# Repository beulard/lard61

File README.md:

# lard61

A custom 60% ansi keyboard PCB.

+ [RP2040](https://www.raspberrypi.com/documentation/microcontrollers/rp2040.html)
+ 4MB flash
+ 12MHz crystal
+ USB-C
+ full n-key rollover
+ a single LED

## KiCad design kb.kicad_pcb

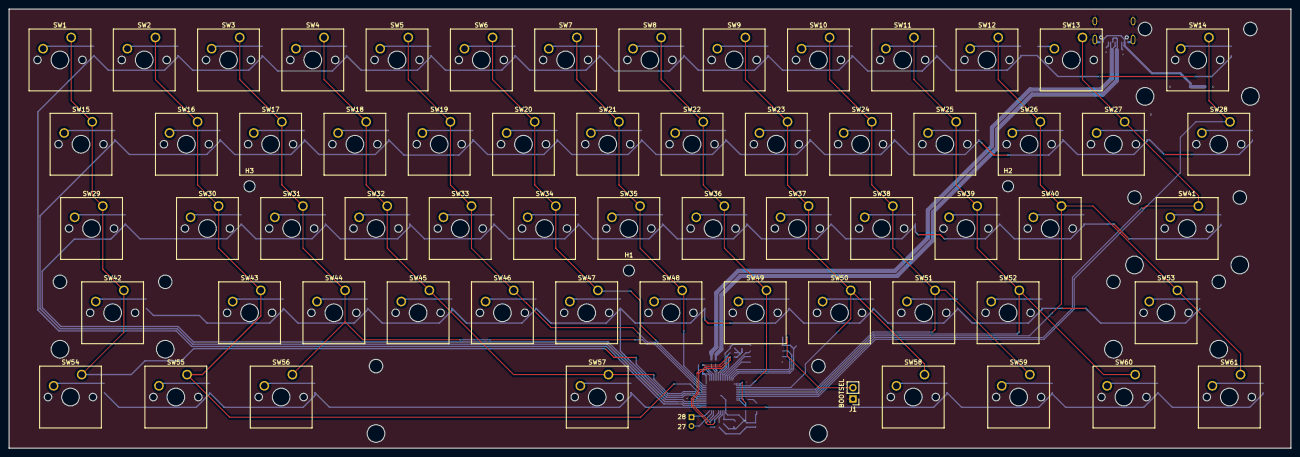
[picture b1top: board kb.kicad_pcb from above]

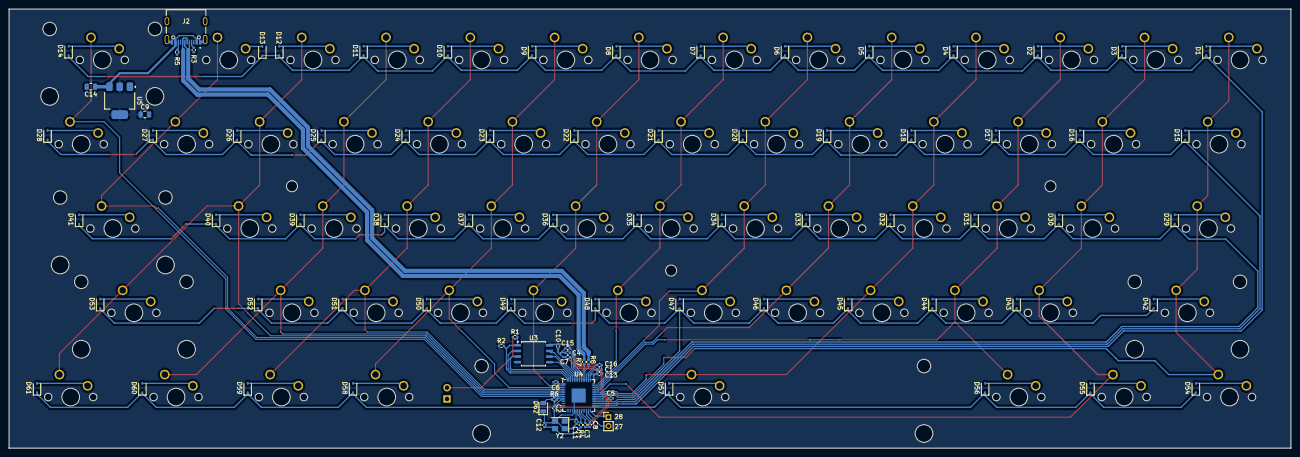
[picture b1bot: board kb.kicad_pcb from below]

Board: 2 copper layers, 289.8 x 99.2 mm, 157 parts (92 on the bottom side), 104 nets.

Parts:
C1, C16: 1u; C_0402_1005Metric
C2, C3, C4, C5, C6, C7, C8, C10, C13, C15: 100n; C_0402_1005Metric
C9, C14: 10u; C_0805_2012Metric
C11, C12: 15p; C_0402_1005Metric
D1, D2, D3, D4, D5, D6, D7, D8, D9, D10, D11, D12, D13, D14, D15, D16, D17, D18, D19, D20, D21, D22, D23, D24, D25, D26, D27, D28, D29, D30, D31, D32, D33, D34, D35, D36, D37, D38, D39, D40, D41, D42, D43, D44, D45, D46, D47, D48, D49, D50, D51, D52, D53, D54, D55, D56, D57, D58, D59, D60, D61: D; D_SOD-323
D62: LED; LED_0805_2012Metric
H1, H2, H3: MountingHole; MountingHole_2.5mm
J1: DNP; PinHeader_1x02_P2.54mm_Vertical
J2: KH-TYPE-C-16P; KINGHELM_KH-TYPE-C-16P
J5: DNP; PinHeader_1x02_P2.00mm_Vertical
R1, R4: 1k; R_0402_1005Metric
R2: DNP; R_0402_1005Metric
R3, R5: 5.1k; R_0402_1005Metric
R6: 470; R_0402_1005Metric
R7, R8: 27.4; R_0402_1005Metric
SW1, SW2, SW3, SW4, SW5, SW6, SW7, SW8, SW9, SW10, SW11, SW12, SW13, SW16, SW17, SW18, SW19, SW20, SW21, SW22, SW23, SW24, SW25, SW26, SW27, SW30, SW31, SW32, SW33, SW34, SW35, SW36, SW37, SW38, SW39, SW40, SW43, SW44, SW45, SW46, SW47, SW48, SW49, SW50, SW51, SW52: DNP; SW_Cherry_MX_1.00u_PCB
SW14: DNP; SW_Cherry_MX_2.00u_PCB
SW15, SW28: DNP; SW_Cherry_MX_1.50u_PCB
SW29: DNP; SW_Cherry_MX_1.75u_PCB
SW41, SW42: DNP; SW_Cherry_MX_2.25u_PCB
SW53: DNP; SW_Cherry_MX_2.75u_PCB
SW54, SW55, SW56, SW58, SW59, SW60, SW61: DNP; SW_Cherry_MX_1.25u_PCB
SW57: DNP; SW_Cherry_MX_6.25u_PCB
U3: W25Q32JVSS; SOIC-8_5.23x5.23mm_P1.27mm
U4: RP2040; QFN-56-1EP_7x7mm_P0.4mm_EP3.2x3.2mm
U5: NCP1117-3.3_SOT223; SOT-223-3_TabPin2
Y2: ABM8-272-T3; Crystal_SMD_Abracon_ABM8G-4Pin_3.2x2.5mm

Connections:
+1V1: C7.1, C8.1, C16.1, U4.23 (DVDD), U4.45 (VREG_VOUT), U4.50 (DVDD)
+3V3: C1.1, C2.1, C3.1, C4.1, C5.1, C6.1, C9.1, C10.1, C13.1, C15.1, R2.1, U3.8 (VCC), U4.1 (IOVDD), U4.10 (IOVDD), U4.22 (IOVDD), U4.26 (RUN), U4.33 (IOVDD), U4.42 (IOVDD), U4.43 (ADC_AVDD), U4.44 (VREG_IN), U4.48 (USB_VDD), U4.49 (IOVDD), U5.2 (VO)
/GPIO0: SW8.1, SW22.1, SW36.1, SW49.1, U4.2 (GPIO0)
/GPIO1: SW9.1, SW23.1, SW37.1, SW50.1, SW58.1, U4.3 (GPIO1)
/GPIO2: SW10.1, SW24.1, SW38.1, SW51.1, SW59.1, U4.4 (GPIO2)
/GPIO3: SW11.1, SW25.1, SW39.1, SW52.1, SW60.1, U4.5 (GPIO3)
/GPIO4: SW12.1, SW26.1, SW40.1, SW53.1, SW61.1, U4.6 (GPIO4)
/GPIO5: SW13.1, SW27.1, SW41.1, U4.7 (GPIO5)
/GPIO6: SW14.1, SW28.1, U4.8 (GPIO6)
/GPIO18: D54.1 (K), D55.1 (K), D56.1 (K), D57.1 (K), D58.1 (K), D59.1 (K), D60.1 (K), D61.1 (K), U4.29 (GPIO18)
/GPIO19: D1.1 (K), D2.1 (K), D3.1 (K), D4.1 (K), D5.1 (K), D6.1 (K), D7.1 (K), D8.1 (K), D9.1 (K), D10.1 (K), D11.1 (K), D12.1 (K), D13.1 (K), D14.1 (K), U4.30 (GPIO19)
/GPIO20: D15.1 (K), D16.1 (K), D17.1 (K), D18.1 (K), D19.1 (K), D20.1 (K), D21.1 (K), D22.1 (K), D23.1 (K), D24.1 (K), D25.1 (K), D26.1 (K), D27.1 (K), D28.1 (K), U4.31 (GPIO20)
/GPIO21: D29.1 (K), D30.1 (K), D31.1 (K), D32.1 (K), D33.1 (K), D34.1 (K), D35.1 (K), D36.1 (K), D37.1 (K), D38.1 (K), D39.1 (K), D40.1 (K), D41.1 (K), U4.32 (GPIO21)
/GPIO22: D42.1 (K), D43.1 (K), D44.1 (K), D45.1 (K), D46.1 (K), D47.1 (K), D48.1 (K), D49.1 (K), D50.1 (K), D51.1 (K), D52.1 (K), D53.1 (K), U4.34 (GPIO22)
/GPIO23: SW1.1, SW15.1, SW29.1, SW42.1, SW54.1, U4.35 (GPIO23)
/GPIO24: SW4.1, SW18.1, SW32.1, SW45.1, SW57.1, U4.36 (GPIO24)
/GPIO25: SW2.1, SW16.1, SW30.1, SW43.1, SW55.1, U4.37 (GPIO25)
/GPIO26: SW3.1, SW17.1, SW31.1, SW44.1, SW56.1, U4.38 (GPIO26_ADC0)
/GPIO27: SW5.1, SW19.1, SW33.1, SW46.1, U4.39 (GPIO27_ADC1)
/GPIO28: SW6.1, SW20.1, SW34.1, SW47.1, U4.40 (GPIO28_ADC2)
/GPIO29: SW7.1, SW21.1, SW35.1, SW48.1, U4.41 (GPIO29_ADC3)
/QSPI_SCLK: U3.6 (CLK), U4.52 (QSPI_SCLK)
/QSPI_SD0: U3.5 (DI(IO0)), U4.53 (QSPI_SD0)
/QSPI_SD1: U3.2 (DO(IO1)), U4.55 (QSPI_SD1)
/QSPI_SD2: U3.3 (IO2), U4.54 (QSPI_SD2)
/QSPI_SD3: U3.7 (IO3), U4.51 (QSPI_SD3)
/QSPI_SS: R1.1, R2.2, U3.1 (~CS), U4.56 (QSPI_SS)
/USB_D+: J2.A6 (DP1), J2.B6 (DP2), R7.2
/USB_D-: J2.A7 (DN1), J2.B7 (DN2), R8.1
/XIN: C11.2, U4.20 (XIN), Y2.1
/XOUT: R4.1, U4.21 (XOUT)
/~USB_BOOT: J1.2, R1.2
GND: C1.2, C2.2, C3.2, C4.2, C5.2, C6.2, C7.2, C8.2, C9.2, C10.2, C11.1, C12.1, C13.2, C14.2, C15.2, C16.2, D62.1 (K), J1.1, J2.A1_B12 (GND), J2.A12_B1 (GND), J2.SH1 (SHIELD), J2.SH2 (SHIELD), J2.SH3 (SHIELD), J2.SH4 (SHIELD), R3.2, R5.1, U3.4 (GND), U4.19 (TESTEN), U4.57 (GND), U5.1 (GND), Y2.2, Y2.4
unnamed: C12.2, R4.2, Y2.3
unnamed: D1.2 (A), SW1.2
unnamed: D2.2 (A), SW3.2
unnamed: D3.2 (A), SW2.2
unnamed: D4.2 (A), SW4.2
unnamed: D5.2 (A), SW5.2
unnamed: D6.2 (A), SW6.2
unnamed: D7.2 (A), SW7.2
unnamed: D8.2 (A), SW8.2
unnamed: D9.2 (A), SW9.2
unnamed: D10.2 (A), SW10.2
unnamed: D11.2 (A), SW11.2
unnamed: D12.2 (A), SW12.2
unnamed: D13.2 (A), SW13.2
unnamed: D14.2 (A), SW14.2
unnamed: D15.2 (A), SW15.2
unnamed: D16.2 (A), SW16.2
unnamed: D17.2 (A), SW17.2
unnamed: D18.2 (A), SW18.2
unnamed: D19.2 (A), SW19.2
unnamed: D20.2 (A), SW20.2
unnamed: D21.2 (A), SW21.2
unnamed: D22.2 (A), SW22.2
unnamed: D23.2 (A), SW23.2
unnamed: D24.2 (A), SW24.2
unnamed: D25.2 (A), SW25.2
unnamed: D26.2 (A), SW26.2
unnamed: D27.2 (A), SW27.2
unnamed: D28.2 (A), SW28.2
unnamed: D29.2 (A), SW29.2
unnamed: D30.2 (A), SW30.2
unnamed: D31.2 (A), SW31.2
unnamed: D32.2 (A), SW32.2
unnamed: D33.2 (A), SW33.2
unnamed: D34.2 (A), SW34.2
unnamed: D35.2 (A), SW35.2
unnamed: D36.2 (A), SW36.2
unnamed: D37.2 (A), SW37.2
unnamed: D38.2 (A), SW38.2
unnamed: D39.2 (A), SW39.2
unnamed: D40.2 (A), SW40.2
unnamed: D41.2 (A), SW41.2
unnamed: D42.2 (A), SW42.2
unnamed: D43.2 (A), SW43.2
unnamed: D44.2 (A), SW44.2
unnamed: D45.2 (A), SW45.2
unnamed: D46.2 (A), SW46.2
unnamed: D47.2 (A), SW47.2
unnamed: D48.2 (A), SW48.2
unnamed: D49.2 (A), SW49.2
unnamed: D50.2 (A), SW50.2
unnamed: D51.2 (A), SW51.2
unnamed: D52.2 (A), SW52.2
unnamed: D53.2 (A), SW53.2
unnamed: D54.2 (A), SW54.2
unnamed: D55.2 (A), SW55.2
unnamed: D56.2 (A), SW56.2
unnamed: D57.2 (A), SW57.2
unnamed: D58.2 (A), SW58.2
unnamed: D59.2 (A), SW59.2
unnamed: D60.2 (A), SW60.2
unnamed: D61.2 (A), SW61.2
unnamed: D62.2 (A), R6.2
unnamed: J2.A5 (CC1), R3.1
unnamed: J2.B5 (CC2), R5.2
unnamed: J5.1, U4.28 (GPIO17)
unnamed: J5.2, U4.27 (GPIO16)
unnamed: R6.1, U4.9 (GPIO7)
unnamed: R8.2, U4.46 (USB_DM)
unnamed: R7.1, U4.47 (USB_DP)
VBUS: C14.1, J2.A4_B9 (VBUS), J2.A9_B4 (VBUS), U5.3 (VI)

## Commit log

2024-05-16 Add KiCad project files
2024-05-16 Add screenshots
2024-06-05 Add pictures of assembled PCB
2024-06-05 Fix back picture path
